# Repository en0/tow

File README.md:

# LED Tug Of War

I created this project with my daughter. She is learning electronics and dreamed up this little
game.

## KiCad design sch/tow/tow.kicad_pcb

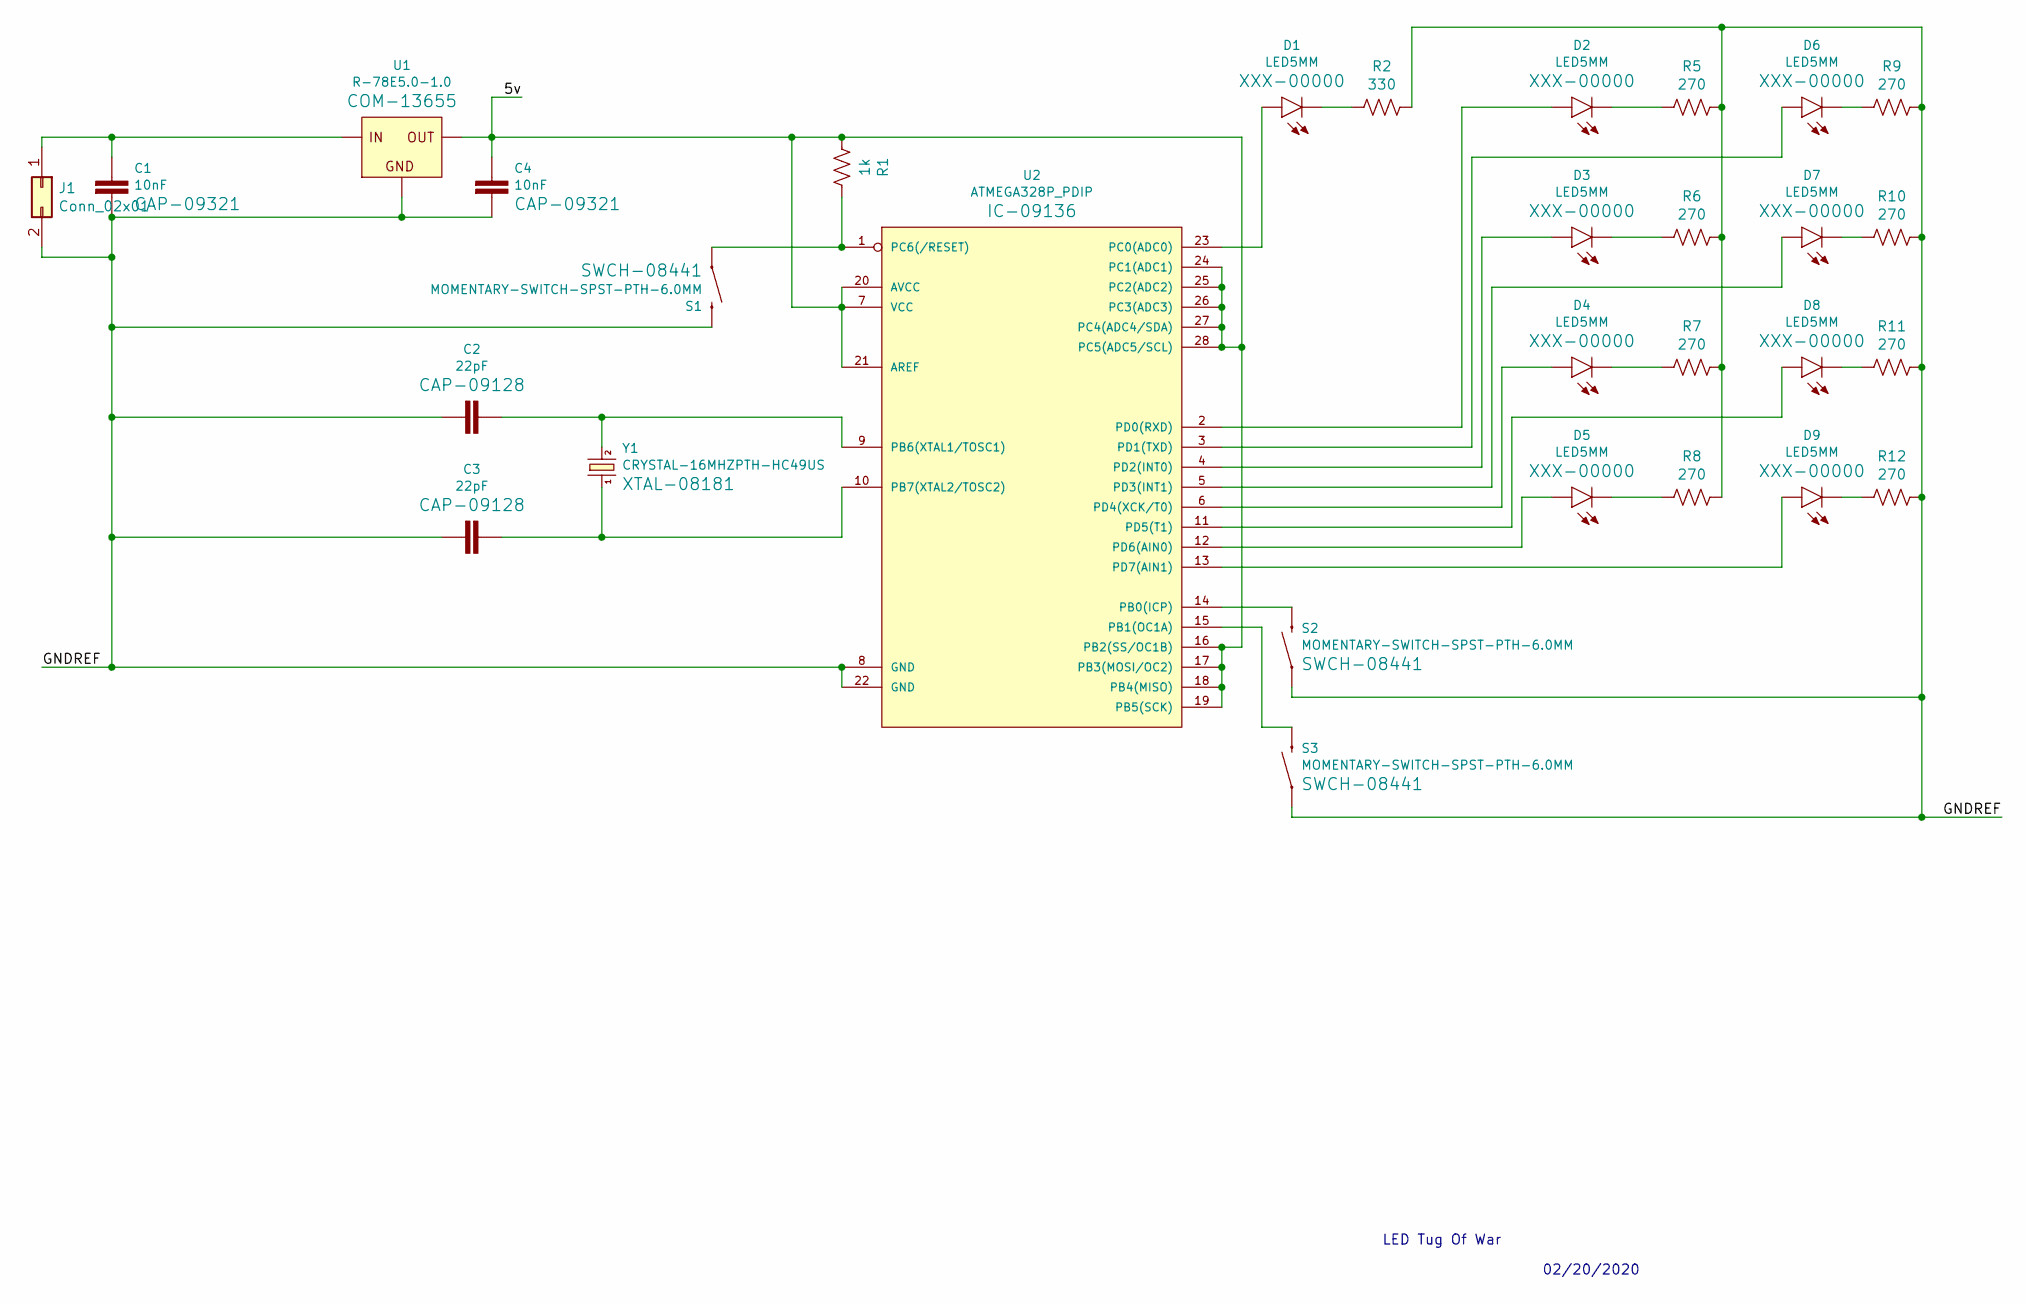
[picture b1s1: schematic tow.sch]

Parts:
C1, C4: 10nF; CAP-PTH-10MM
C2, C3: 22pF; CAP-PTH-2.54
D1, D2, D3, D4, D5, D6, D7, D8, D9: LED5MM; LED_5MM
J1: Conn_02x01; PinHeader_2x01_P2.54mm_Vertical
R1: 1k; R_Axial_DIN0207_L6.3mm_D2.5mm_P10.16mm_Horizontal
R2: 330; R_Axial_DIN0207_L6.3mm_D2.5mm_P10.16mm_Horizontal
R5, R6, R7, R8, R9, R10, R11, R12: 270; R_Axial_DIN0207_L6.3mm_D2.5mm_P10.16mm_Horizontal
S1, S2, S3: MOMENTARY-SWITCH-SPST-PTH-6.0MM; TACTILE_SWITCH_PTH_6.0MM
U1: R-78E5.0-1.0; DC-DC_CONVERTER_78XX
U2: ATMEGA328P_PDIP; DIP28
Y1: CRYSTAL-16MHZPTH-HC49US; HC49US

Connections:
/5v: C4.1, R1.2, U1.VOUT (OUT), U2.7 (VCC), U2.16 (PB2(SS/OC1B)), U2.17 (PB3(MOSI/OC2)), U2.18 (PB4(MISO)), U2.19 (PB5(SCK)), U2.20 (AVCC), U2.21 (AREF), U2.24 (PC1(ADC1)), U2.25 (PC2(ADC2)), U2.26 (PC3(ADC3)), U2.27 (PC4(ADC4/SDA)), U2.28 (PC5(ADC5/SCL))
/GNDREF: C1.2, C2.2, C3.2, C4.2, J1.2, R2.1, R5.1, R6.1, R7.1, R8.1, R9.1, R10.1, R11.1, R12.1, S1.3 (2), S2.1, S3.1, U1.GND, U2.8 (GND), U2.22 (GND)
unnamed: C1.1, J1.1, U1.VIN (IN)
unnamed: C2.1, U2.9 (PB6(XTAL1/TOSC1)), Y1.2
unnamed: C3.1, U2.10 (PB7(XTAL2/TOSC2)), Y1.1
unnamed: D1.A, U2.23 (PC0(ADC0))
unnamed: D1.K (C), R2.2
unnamed: D2.A, U2.2 (PD0(RXD))
unnamed: D2.K (C), R5.2
unnamed: D3.A, U2.4 (PD2(INT0))
unnamed: D3.K (C), R6.2
unnamed: D4.A, U2.6 (PD4(XCK/T0))
unnamed: D4.K (C), R7.2
unnamed: D5.A, U2.12 (PD6(AIN0))
unnamed: D5.K (C), R8.2
unnamed: D6.A, U2.3 (PD1(TXD))
unnamed: D6.K (C), R9.2
unnamed: D7.A, U2.5 (PD3(INT1))
unnamed: D7.K (C), R10.2
unnamed: D8.A, U2.11 (PD5(T1))
unnamed: D8.K (C), R11.2
unnamed: D9.A, U2.13 (PD7(AIN1))
unnamed: D9.K (C), R12.2
unnamed: R1.1, S1.1, U2.1 (PC6(/RESET))
unnamed: S2.3 (2), U2.14 (PB0(ICP))
unnamed: S3.3 (2), U2.15 (PB1(OC1A))

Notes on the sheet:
LED Tug Of War
02/20/2020

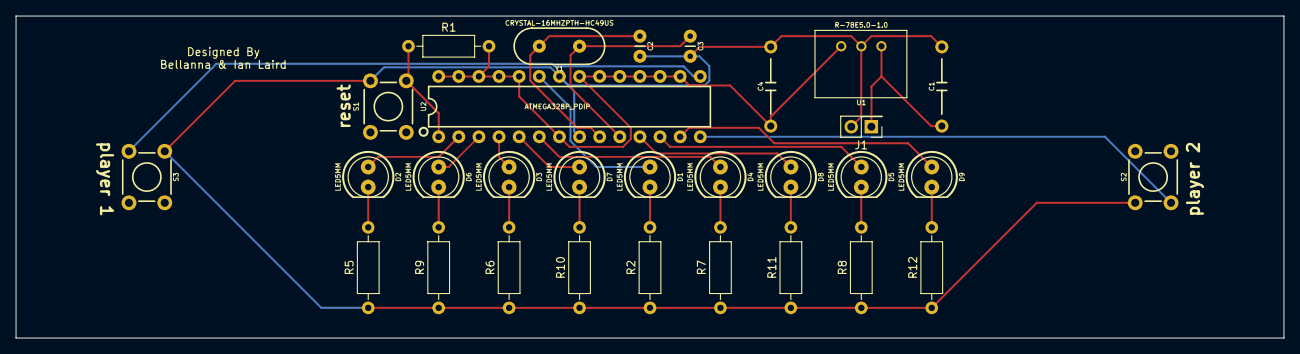
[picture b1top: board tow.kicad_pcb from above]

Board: 2 copper layers, 160.0 x 40.6 mm, 30 parts (0 on the bottom side), 26 nets.

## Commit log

2022-01-09 Updated PCB
